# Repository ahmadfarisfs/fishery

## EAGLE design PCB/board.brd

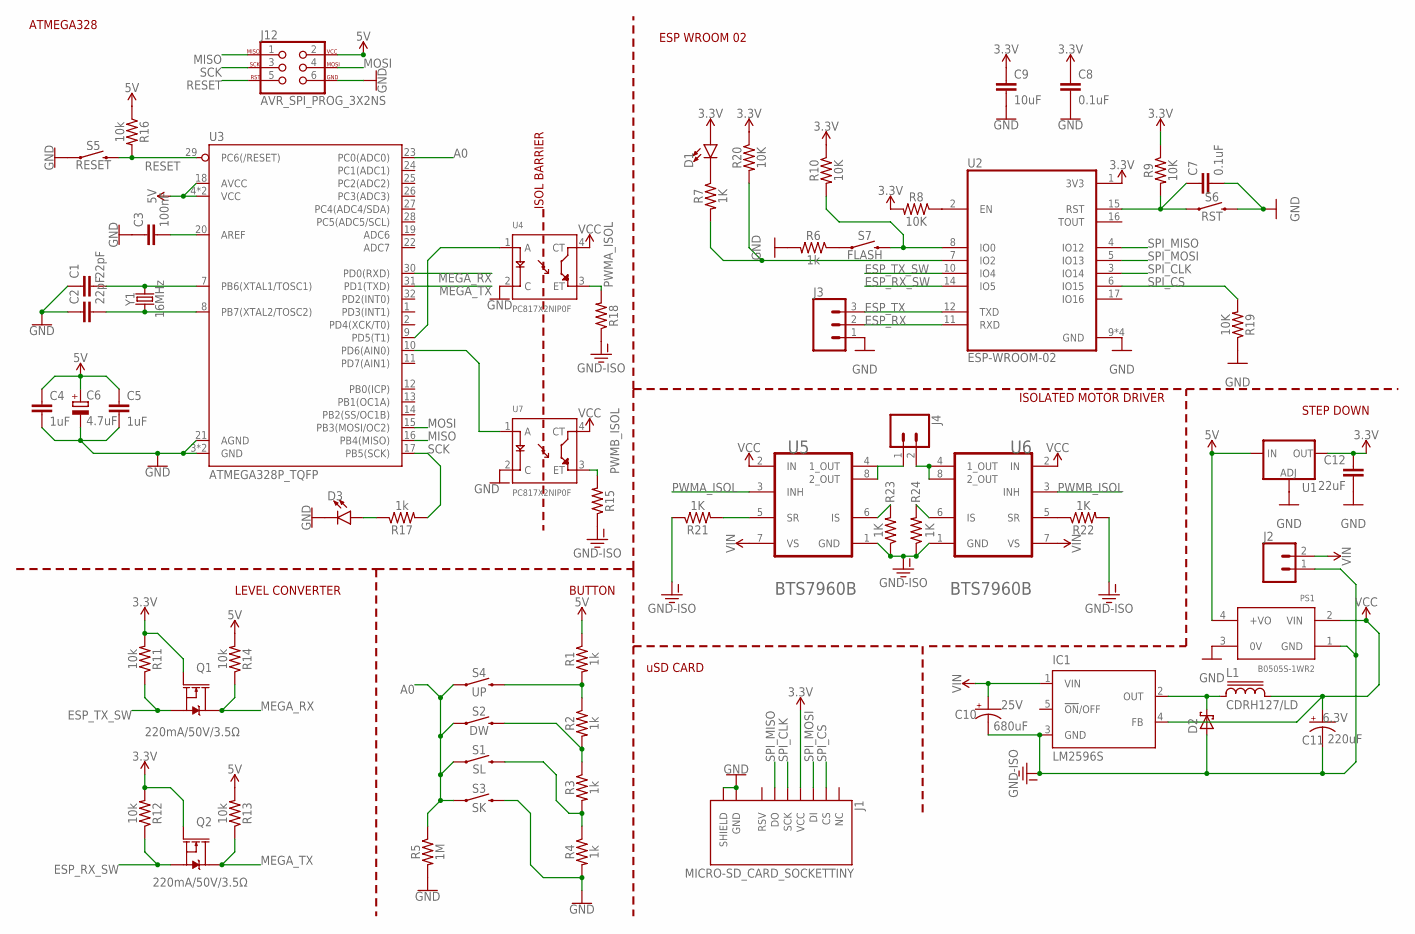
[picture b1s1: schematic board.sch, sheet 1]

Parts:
C1, C2: 22pF; 0603
C3: 100nF; C0805
C4, C5: 1uF; C0805
C6: 4.7uF; UD-4X5,8_NICHICON
C7, C8: 0.1uF; 0603
C9: 10uF; 0603
C10: 680uF; E5-10,5; VOLTAGE 25V
C11: 220uF; UD-6,3X5,8_NICHICON; VOLTAGE 6.3V
C12: 22uF; 0805
D1, D3: LED1206; LED-1206
D2: SCHOTTKY-DIODESMD; SMB
IC1: LM2596S; TO263-5
J1: MICRO-SD_CARD_SOCKETTINY; MICROSD_TINY
J2, J4: CONN_025MM; SCREWTERMINAL-5MM-2
J3: CONN_03POLAR; MOLEX-1X3
J12: AVR_SPI_PROG_3X2NS; 2X3-NS
L1: CDRH127/LD
PS1: B0505S-1WR2; CONV_B0505S-1WR2
Q1, Q2: 220mA/50V/3.5Ω; SOT23-3
R1, R2, R3, R4, R6, R17: 1k; 1206
R5: 1M; 1206
R7, R21, R22, R23, R24: 1K; 1206
R8, R9, R10, R19, R20: 10K; 1206
R11, R12, R13, R14, R16: 10k; 1206
R15, R18: 1206
S1: SL; TACTILE_SWITCH_SMD_5.2MM
S2: DW; TACTILE_SWITCH_SMD_5.2MM
S3: SK; TACTILE_SWITCH_SMD_5.2MM
S4: UP; TACTILE_SWITCH_SMD_5.2MM
S5: RESET; TACTILE_SWITCH_SMD_5.2MM
S6: RST; TACTILE_SWITCH_SMD_5.2MM
S7: FLASH; TACTILE_SWITCH_SMD_5.2MM
U1: V_REG_LM1117SOT223; SOT223
U2: ESP-WROOM-02; MODULE_ESP-WROOM-02
U3: ATMEGA328P_TQFP; TQFP32-08
U4, U7: PC817X2NIP0F; SOT254P975X400-4N
U5, U6: INFINEON_BTS7960BINFINEON_BTS7960B_0_2; INFINEON_BTS7960B_2
Y1: 16MHz; HC49US

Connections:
3.3V: C8.1, C9.1, C12.1, D1.A, J1.4 (VCC), Q1.1 (G), Q2.1 (G), R8.2, R9.1, R10.1, R11.2, R12.2, R20.1, U1.2 (OUT), U1.4 (OUT), U2.1 (3V3)
5V: C4.1, C5.1, C6.+, J12.2, PS1.4 (+VO), R1.1, R13.2, R14.2, R16.1, U1.3 (IN), U3.4 (VCC), U3.6 (VCC), U3.18 (AVCC)
A0: R5.1, S1.1, S1.2 (1), S2.1, S2.2 (1), S3.1, S3.2 (1), S4.1, S4.2 (1), U3.23 (PC0(ADC0))
ESP_RX: J3.2, U2.11 (RXD)
ESP_RX_SW: Q2.2 (S), R12.1, U2.14 (IO5)
ESP_TX: J3.3, U2.12 (TXD)
ESP_TX_SW: Q1.2 (S), R11.1, U2.10 (IO4)
GND: C1.1, C2.1, C3.1, C4.2, C5.2, C6.-, C7.2, C8.2, C9.2, C12.2, D3.C, J1.6 (GND), J1.GND1 (SHIELD), J1.GND2 (SHIELD), J1.GND3 (SHIELD), J1.GND4 (SHIELD), J1.GND5 (SHIELD), J1.GND6 (SHIELD), J3.1, J12.6, PS1.3 (0V), R4.2, R5.2, R6.2, R19.1, S3.3 (2), S3.4 (2), S5.1, S5.2 (1), S6.3 (2), S6.4 (2), U1.1 (ADJ), U2.9 (GND), U2.13 (GND), U2.18 (GND), U2.19 (GND), U3.3 (GND), U3.5 (GND), U3.21 (AGND), U4.2 (C), U7.2 (C)
GND-ISO: C10.-, C11.-, D2.A, IC1.3 (GND), J2.1, PS1.1 (GND), R15.1, R18.1, R21.1, R22.2, R23.1, R24.1, U5.1 (GND), U6.1 (GND)
MEGA_RX: Q1.3 (D), R14.1, U3.30 (PD0(RXD))
MEGA_TX: Q2.3 (D), R13.1, U3.31 (PD1(TXD))
MISO: J12.1, U3.16 (PB4(MISO))
MOSI: J12.4, U3.15 (PB3(MOSI/OC2))
unnamed: C1.2, U3.7 (PB6(XTAL1/TOSC1)), Y1.2
unnamed: C2.2, U3.8 (PB7(XTAL2/TOSC2)), Y1.1
unnamed: R2.2, R3.1, S2.3 (2), S2.4 (2)
unnamed: R3.2, R4.1, S1.3 (2), S1.4 (2)
unnamed: R1.2, R2.1, S4.3 (2), S4.4 (2)
unnamed: R23.2, U5.6 (IS)
unnamed: C7.1, R9.2, S6.1, S6.2 (1), U2.15 (RST)
unnamed: R24.2, U6.6 (IS)
unnamed: R10.2, S7.3 (2), S7.4 (2), U2.8 (IO0)
unnamed: R6.1, S7.1, S7.2 (1)
unnamed: J4.1, U5.4 (1_OUT), U5.8 (2_OUT)
unnamed: D1.C, R7.1
unnamed: R8.1, U2.2 (EN)
unnamed: J4.2, U6.4 (1_OUT), U6.8 (2_OUT)
unnamed: R21.2, U5.5 (SR)
unnamed: R7.2, R20.2, U2.7 (IO2)
unnamed: R22.1, U6.5 (SR)
unnamed: D3.A, R17.1
unnamed: C3.2, U3.20 (AREF)
OUT: D2.C, IC1.2 (OUT), L1.1
PWMA: U3.9 (PD5(T1)), U4.1 (A)
PWMA_ISOL: R18.2, U4.3 (ET), U5.3 (INH)
PWMB: U3.10 (PD6(AIN0)), U7.1 (A)
PWMB_ISOL: R15.2, U6.3 (INH), U7.3 (ET)
RESET: J12.5, R16.2, S5.3 (2), S5.4 (2), U3.29 (PC6(/RESET))
SCK: J12.3, R17.2, U3.17 (PB5(SCK))
SPI_CLK: J1.5 (SCK), U2.3 (IO14)
SPI_CS: J1.2 (CS), R19.2, U2.6 (IO15)
SPI_MISO: J1.7 (DO), U2.4 (IO12)
SPI_MOSI: J1.3 (DI), U2.5 (IO13)
VCC: C11.+, IC1.4 (FB), L1.2, PS1.2 (VIN), U4.4 (CT), U5.2 (IN), U6.2 (IN), U7.4 (CT)
VIN: C10.+, IC1.1 (VIN), J2.2, U5.7 (VS), U6.7 (VS)

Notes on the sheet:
LEVEL CONVERTER
ATMEGA328
BUTTON
ESP WROOM 02
uSD CARD
ISOLATED MOTOR DRIVER
STEP DOWN
ISOL BARRIER

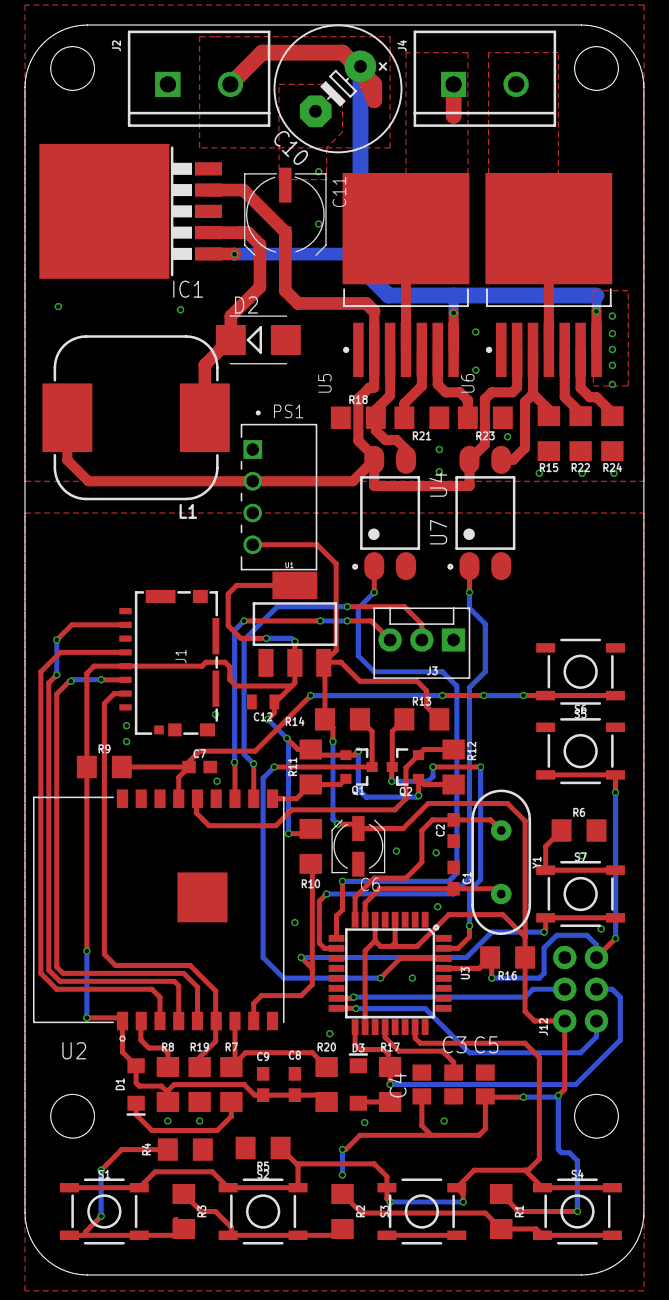
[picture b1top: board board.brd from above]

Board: 2 copper layers, 49.5 x 100.0 mm, 64 parts (0 on the bottom side), 45 nets.

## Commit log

2020-08-17 leftover files

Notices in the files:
parts and their libraries:
SparkFun-IC-Microcontroller: Licensing: Creative Commons ShareAlike 4.0 International - https://creativecommons.org/licenses/by-sa/4.0
inductor-sumida: Copyright (C) 2008, Bob Starr
